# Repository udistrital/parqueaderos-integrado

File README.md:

#Parqueaderos
Es el entorno de desarrollo para el sistema de parqueaderos. Esta se inicia a través de un entorno de Vagrant.

Para iniciar la máquina:
```bash
$ vagrant up
```

Se ejecuta el aprovisionamiento de software base a la máquina:
```bash
$ vagrant provision
$ vagrant reload
$ vagrant ssh
```

¿MÁS FÁCIL?
-----------
```bash
$ ./install
```

INICIAR
-------
```bash
$ ./run
```

OTRAS OPCIONES
--------------
```bash
$ ./run --help
```

MODELO
------

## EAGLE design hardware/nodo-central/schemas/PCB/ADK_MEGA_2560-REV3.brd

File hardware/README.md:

# Módulo WIFI ESP8266
--------------------
Este módulo se comunica por protocolo serial (UART http://www.mbedded.ninja/electronics/communication-protocols/uart-protocol) a una taza predeterminada de 115200 baudios (bits por segundo https://www.arduino.cc/en/Serial/Begin).

* Guía rápida de inicio con el módulo WiFi ESP8266, contiene recomendaciones, conexiones y ejemplo de comandos AT se usa con Arduino UNO pero no se recomienda alimentación desde esta, se da alternativamente instrucciones para FTDI 3.3V Board. http://rancidbacon.com/files/kiwicon8/ESP8266_WiFi_Module_Quick_Start_Guide_v_1.0.4.pdf
* Se da una presentación de conexión de pines completa para todo el módulo, se realiza también una forma de actualizar el firmware del dispositivo. http://www.instructables.com/id/The-First-Usage-of-ESP8266-With-Arduino-Uno/
* Se destaca por dar un ejemplo de comandos AT. http://rayshobby.net/first-impression-on-the-esp8266-serial-to-wifi-module/
* Es el datasheet del integrado base, se destaca la muestra de potencia consumida en modo Transmisor, Receptor y en estados de hibernación. http://www.electroschematics.com/wp-content/uploads/2015/02/esp8266-datasheet.pdf
* Muestra de otra forma la documentación habitual, tiene documentación de los comandos AT sin ejemplos. https://nurdspace.nl/ESP8266
* Conexión del módulo for dummies (torpes). http://www.teomaragakis.com/hardware/electronics/how-to-connect-an-esp8266-to-an-arduino-uno/
* Se muestra un mapa conceptual de los comandos AT con ejemplos y una lista extendida de ellos. Referencias de documentación, características técnicas y la forma de actualizar el firmware. https://www.itead.cc/wiki/ESP8266_Serial_WIFI_Module
* Contiene información necesaria para configurar el módulo como un Access Point. http://dominicm.com/esp8266-configure-access-point/
* La wiki definitiva para los comandos AT: https://github.com/espressif/ESP8266_AT/wiki

# Módulo Ultrasonido MB1010 LV-MaxSonar®-EZ1
-------------------------------------------
Este módulo se utiliza para detectar la presencia o ausencia de objetos, este se puede controlar por medio de 3 métodos, el análogo, el PWM y con comunicación serial. El más acosejable es PWM (http://playground.arduino.cc/Main/MaxSonar).

* Documentación oficial de implementación del sensor. http://www.maxbotix.com/articles/085.htm
* Características técnicas del dispositivo sumado a enlaces del datasheet, explicaciones, guía de selección del sensores de la misma familia. https://www.sparkfun.com/products/8502
* https://sheldondwill.wordpress.com/2014/02/04/using-an-ultrasonic-sensor-hc-sr04-with-a-3-3v-micro-controller-tiva-c-series/

# Módulo RF 433MHz Transmisor y Receptor
---------------------------------------
* Enlaces de un transmisor RF dirigido a muchos Receptores. https://www.youtube.com/watch?v=h3OevEdl674 https://github.com/Simsso/Arduino-Wireless-Module-Multiple-Receivers
* Ideas de cómo conectar 20 sensores wireless a un solo receptor. Un transmisor solo emite cuando es necesario y puede retransmitir algunas veces con base de tiempo aleatorio para asegurarse de la llegada del dato. Las colisiones son bajas si la concurrencia de eventos no es baja. Se puede también transmitir a diferentes bases de tiempo para reducir el número de colisiones. http://electronics.stackexchange.com/questions/74272/how-to-connect-20-wireless-sensors-in-one-receiver-with-arduino
* Uso de la biblioteca rc-switch que sirve enviar códigos RC, sirve para controlar dispositivos de radio remoto. En este se consigue la información de 3 sensores de temperatura remotos para hacer un promedio de temperatura, se utilizan arduinos nano v3 y un display I2C, se muestra el código. http://www.electronicsmayhem.com/?p=68 https://github.com/sui77/rc-switch
* RF Link Receiver - 4800bps (434MHz), 500ft (152.4m) rango (en las mejores condiciones), 4800bps data rate, 5V supply voltage. https://www.sparkfun.com/products/10532
* RF Link Transmitter - 434MHz, 500ft (152.4m) rango (en las mejores condiciones), 4800bps data rate, 5V supply voltage. https://www.sparkfun.com/products/10534
* Tutorial completo de módulos RF para Arduino, código, conexiones y vídeos. http://www.instructables.com/id/RF-315433-MHz-Transmitter-receiver-Module-and-Ardu/?ALLSTEPS
* Breve documentación de la biblioteca VirtualWire. http://www.pjrc.com/teensy/td_libs_VirtualWire.html
* Se destaca por tener una comparación de dispositivos de Radio Frecuencia "económicos". http://www.raviyp.com/embedded/152-low-cost-zigbee-modules-for-using-in-projects
* 11 protocolos de internet de las cosas (IoT) sobre los que usted necesita saber. https://www.rs-online.com/designspark/eleven-internet-of-things-iot-protocols-you-need-to-know-about
* Hardware abierto para internet de las cosas. http://www.postscapes.com/internet-of-things-hardware/

# NRF24L01 transceptor 2.4-2.5GHz en la banda ISM (Industrial, Científico, Médico)
Este módulo transmite y recibe datos. Tiene un bajo consumo de potencia y el rango de trabajo del tensión es de 1.9 hasta 3.6 voltios. Tiene multiples frecuencas (125 puntos).
* https://hallard.me/nrf24l01-real-life-range-test/
* https://github.com/maniacbug/RF24
* https://harizanov.com/2013/06/nrf24l01-range-testing/
* http://playground.arduino.cc/InterfacingWithHardware/Nrf24L01
* https://arduino-info.wikispaces.com/Nrf24L01-Info
* http://www.nordicsemi.com/eng/Products/2.4GHz-RF/nRF24L01
* https://arduino-info.wikispaces.com/Nrf24L01-2.4GHz-HowTo?responseToken=fcd06dad835d084c7d89d1d4a147b989
* http://howtomechatronics.com/tutorials/arduino/arduino-wireless-communication-nrf24l01-tutorial/
* http://projectsfromtech.blogspot.com.co/2013/05/nrf24l01-arduino-communication-on.html
* http://howtomechatronics.com/tutorials/arduino/arduino-wireless-communication-nrf24l01-tutorial/
* http://projectsfromtech.blogspot.com.co/2013/05/nrf24l01-arduino-communication-on.html
* http://forum.arduino.cc/index.php?topic=131078.msg1331019#msg1331019

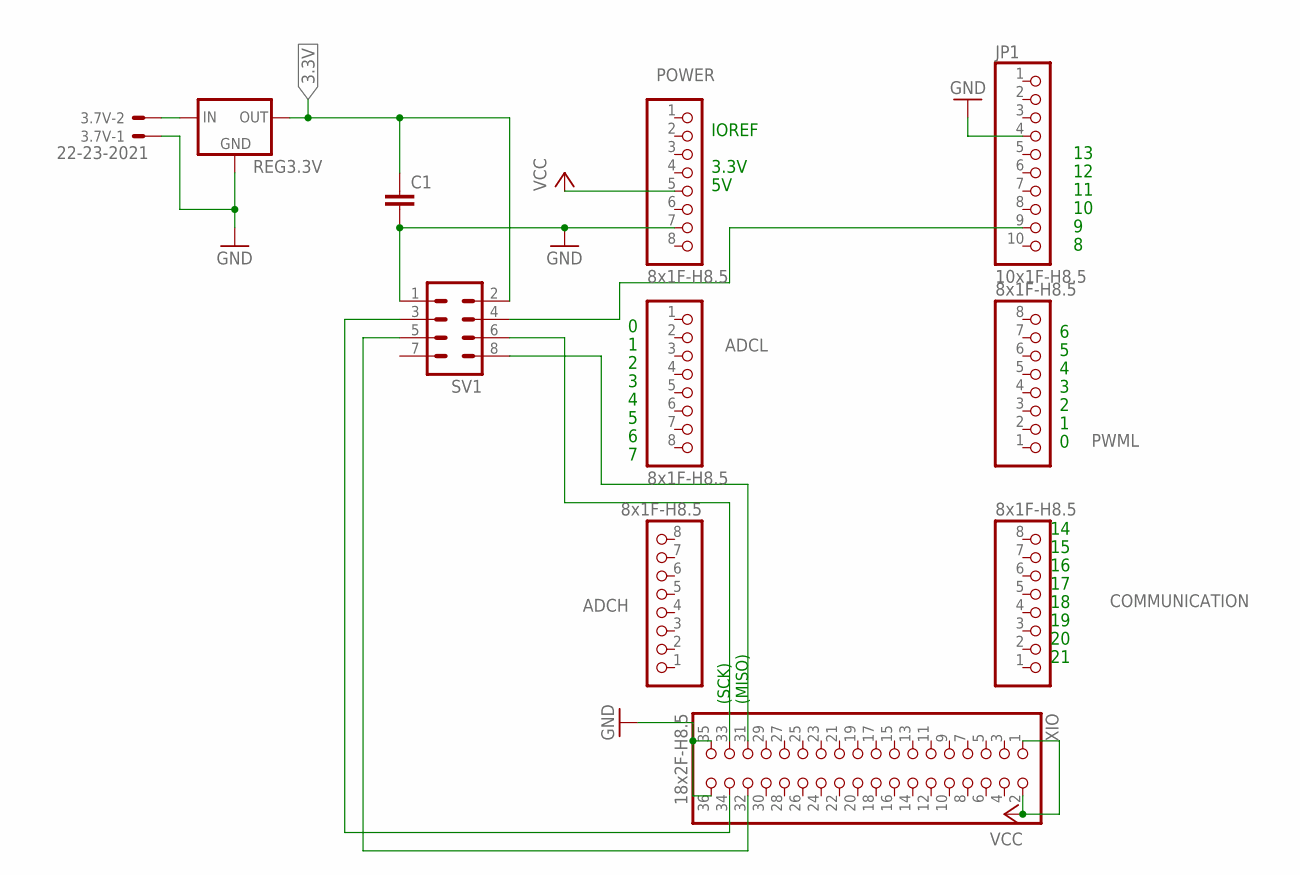
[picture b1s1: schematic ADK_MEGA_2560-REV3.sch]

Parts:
3.7V: 22-23-2021
ADCH: 8x1F-H8.5; 1X08
ADCL: 8x1F-H8.5; 1X08
C1: C-EU025-025X050; C025-025X050
COMMUNICATION: 8x1F-H8.5; 1X08
JP1: 10x1F-H8.5; 1X10
POWER: 8x1F-H8.5; 1X08
PWML: 8x1F-H8.5; 1X08
REG3.3V: 78XXL
SV1: MA04-2
XIO: 18x2F-H8.5; 2X18

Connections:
3.3V: C1.1, REG3.3V.OUT, SV1.2
GND: 3.7V.1, C1.2, JP1.4, POWER.7, REG3.3V.GND, SV1.1, XIO.35, XIO.36
unnamed: SV1.3, XIO.34
unnamed: SV1.5, XIO.32
unnamed: JP1.9, SV1.4
unnamed: SV1.6, XIO.33
unnamed: SV1.8, XIO.31
unnamed: 3.7V.2, REG3.3V.IN
VCC: POWER.5, XIO.1, XIO.2

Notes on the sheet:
(SCK)
(MISO)
IOREF
3.3V

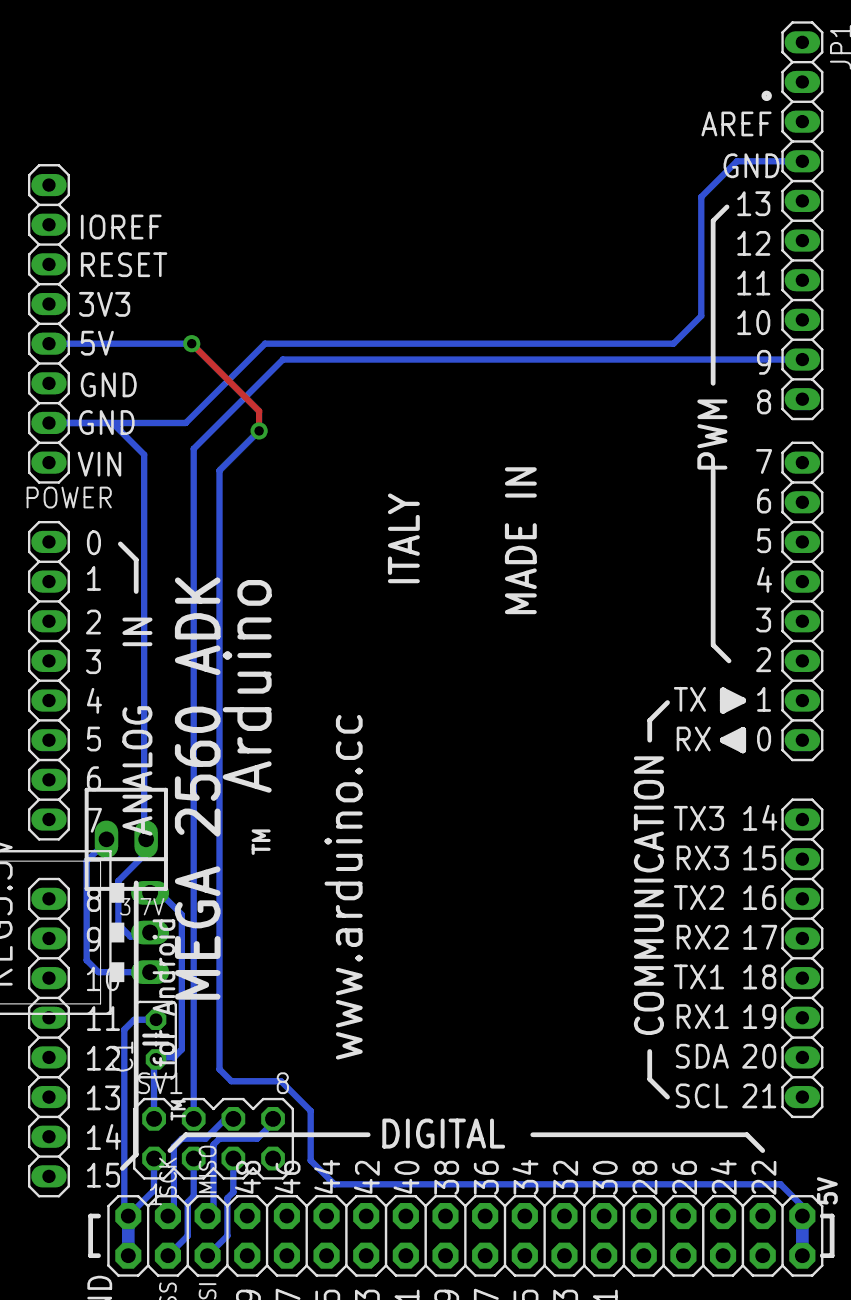
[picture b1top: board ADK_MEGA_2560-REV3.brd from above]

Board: 2 copper layers, 11 parts (0 on the bottom side), 9 nets.

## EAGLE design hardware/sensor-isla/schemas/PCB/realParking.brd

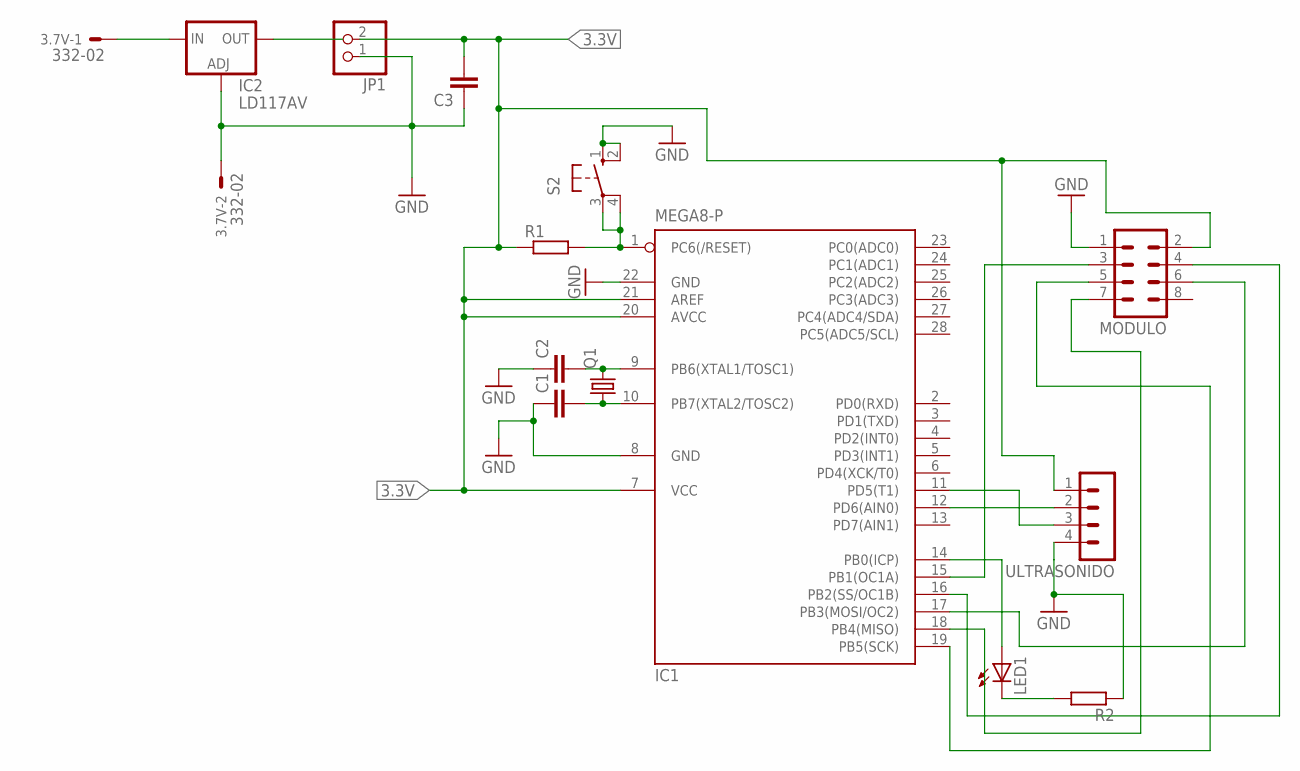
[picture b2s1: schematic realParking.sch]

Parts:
3.7V: 332-02
C1, C2, C3: C2,5-3; C2.5-3
IC1: MEGA8-P; DIL28-3
IC2: LD117AV; TO220L1
JP1: PINHD-1X2; 1X02
LED1: LED5MM
MODULO: MA04-2
Q1: CRYSTALTC26V; TC26V
R1, R2: R-EU_0204/5; 0204/5
S2: 10-XX; B3F-10XX
ULTRASONIDO: MA04-1

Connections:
3.3V: C3.2, IC1.7 (VCC), IC1.20 (AVCC), IC1.21 (AREF), JP1.2, MODULO.2, R1.1, ULTRASONIDO.1
GND: 3.7V.2, C1.1, C2.1, C3.1, IC1.8 (GND), IC1.22 (GND), IC2.1 (ADJ), JP1.1, MODULO.1, R2.1, S2.1 (S), S2.2 (S1), ULTRASONIDO.4
unnamed: 3.7V.1, IC2.3 (IN)
unnamed: IC1.12 (PD6(AIN0)), ULTRASONIDO.2
unnamed: IC1.11 (PD5(T1)), ULTRASONIDO.3
unnamed: LED1.K (C), R2.2
unnamed: IC1.14 (PB0(ICP)), LED1.A
unnamed: IC1.15 (PB1(OC1A)), MODULO.3
unnamed: IC1.16 (PB2(SS/OC1B)), MODULO.4
unnamed: IC1.17 (PB3(MOSI/OC2)), MODULO.6
unnamed: IC1.18 (PB4(MISO)), MODULO.7
unnamed: IC1.19 (PB5(SCK)), MODULO.5
unnamed: C2.2, IC1.9 (PB6(XTAL1/TOSC1)), Q1.2
unnamed: C1.2, IC1.10 (PB7(XTAL2/TOSC2)), Q1.1
unnamed: IC1.1 (PC6(/RESET)), R1.2, S2.3, S2.4 (P1)

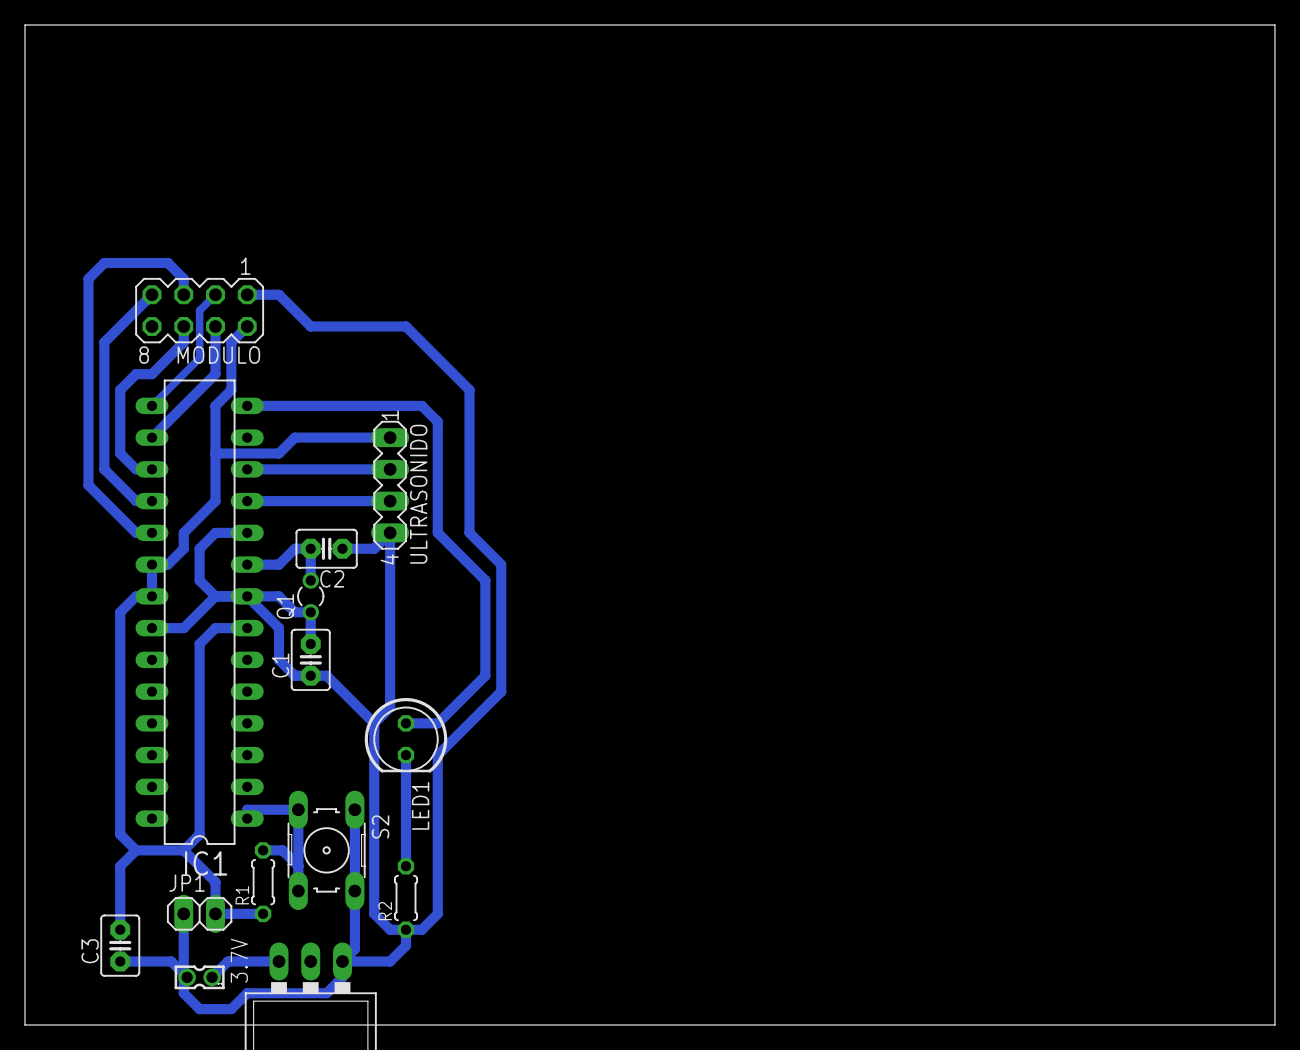
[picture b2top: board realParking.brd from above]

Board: 2 copper layers, 100.0 x 80.0 mm, 14 parts (0 on the bottom side), 15 nets.

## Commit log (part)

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2016-06-08 Se organizan los ficheros
2016-06-25 cambios para proxy
2016-06-25 Script funcionando
2016-07-12 ORM de Primera Propuesta de BD
2016-07-13 Se genera script de instalación de postgresql y script de parqueaderos
2016-07-13 Se mejoran los scripts y se corrigen sus errores
2016-07-13 Se generan otras utilidades
2016-07-14 Activacion de Migracion de DB
2016-07-18 mejoras a script instalación postgres, ip única
2016-07-18 Separando a virtualbox guest aditions en otro fichero
2016-07-18 fix postgresql instalation
2016-07-19 Se cambia la carpeta de desarrollo de data por src, ademas se realiza la segunda entrega de los ORM de la nueva base de datos propuesta, a traves de la modificacion del framework de beego.
2016-07-19 Ejecución de instrucción de construcción de tabla en una sola línea
2016-07-19 Se crea script de instalación del entorno
2016-07-19 Funciones para poner el proxy_ud
2016-07-19 Se actualiza para que cargue instalación de vboxaditions solo en caso de que el proveedor sea vbox
2016-07-19 Se quita beego
2016-07-19 compilación auto bee tool y mejora proxy_ud
2016-07-23 Se agregan las instruccion para comprobar el CRUD desde el backend
2016-07-23 Se relanza la version ReleaseTwo con las modificaciones ya comentadas para comprobar su funcionalidad quedando habilitada la misma
2016-07-26 actualizando readme
2016-07-30 Se reconfigura el Backend para funcionamiento con el Frontend (cors)
2016-07-30 Creacion del CRUD para el frontend con angularjs
2016-07-30 javascript con los controladores para el sitio web con ngResource para el consumo de RESTFull
2016-07-30 Template html basado en el layout general del sitio index.html, donde se muestran todos lor registros de la tabla de tipo_propietario
2016-07-30 Template html para la gestion de un registro en particular (ver, editar o eliminar) de la tabla tipo_propietario
2016-07-30 Captura de pantalla mostranto respuesta de Get One
2016-07-30 Captura de pantalla mostranto respuesta de Put
2016-08-03 Sistema de construcción de CRUD con yeoman
2016-08-05 Se mapean puertos y se instalan utilidades
2016-08-05 Se anexa prueba de uso de la herramiento generator-angular-go-martini
2016-08-05 directorios bin y pkg
2016-08-05 El paquete w3m no está en los repos, causaba fallo en la instalación
2016-08-05 script para instalar utilidades de npm
2016-08-05 Se crea script que crea automáticamente la base de datos
2016-08-05 El SQL debe estar disponible para ser modificado desde la máquina
2016-08-07 Se actualiza el readme
2016-08-07 Se agrega web-server en la ejecución del comando $ gulp
2016-08-08 Comandos ejecutados en la creación de CRUD tipo_propietario
2016-08-08 Fix permisos sobre db y selección db
2016-08-08 Comandos ejecutados para la creación de una API temporal para pruebas CRUD
2016-08-08 Registro de Yeoman generador CRUD
2016-08-08 Un script con instrucciones de uso del cliente
2016-08-08 Se actualiza el modelo de la base de datos en donde se definio para cada tabla como llave primario un dato indice
2016-08-08 Se agrega la v.1 del ORM para propietario (con las caracteristicas de los datos funcionando)
2016-08-08 Se agrega la v.1 del ORM para grupo_isla (con las caracteristicas de los datos funcionando)
2016-08-08 Se agrega la v.1 del ORM para grupo_isla (con las caracteristicas de los datos funcionando y los json completos)
2016-08-08 Se agrega la v.1 de la documentacion gestor de enrutamiento del backend
2016-08-08 Se elimina modelo de bases de datos anterior
2016-08-08 Se agrega v1 del controlador para la tabla propietario
2016-08-08 Se agrega v1 del controlador para la tabla grupo_isla
2016-08-08 Se agrega gestor de documentacion v1 del proyecto
2016-08-08 Se agrega codigo fuente y binario principal del proyecto v1 (el main del proyecto)
2016-08-08 Se agrega el fuente de bee/g_addcode.go modificado por particularidades del proyecto
2016-08-08 Se agregar gestores para la creacion de Frontend utilizando el generador de martini-go-angular
2016-08-08 Se agrega las librerias necesarios para el funcionamiento de FrontEnd (como las dependencia de AngularJs)
2016-08-08 Se agrega los estilos del FrontEnd
2016-08-08 Se agrega el template para propietario (CRUD) del FrontEnd
2016-08-08 Se agrega el template para grupo_isla (CRUD) del FrontEnd
2016-08-08 Se agrega el template para home del FrontEnd
2016-08-08 Se agrega el controlador para home del FrontEnd
2016-08-08 Se agrega el enrutador, controlador y la descripcion del servicio a consumir (REST-Full API) para propietario del FrontEnd
2016-08-08 Se agrega el enrutador, controlador y la descripcion del servicio a consumir (REST-Full API) para grupo-isla del FrontEnd
2016-08-11 Se agrega la restriccion de valores para IdTipoPropietario en la tabla Propietario (con select), como mecanismo de validacion de datos
2016-08-11 Se agrega la restriccion de valores para IdPropietario en la tabla Vehiculo (con select), como mecanismo de validacion de datos en la vista en el controller
2016-08-11 Se agrega la restriccion de valores para IdVehiculo y IdGrupoIsla en la tabla Isla (con select), como mecanismo de validacion de datos en la vista controller
2016-08-11 Para pruebas se deja sin CORS
2016-08-11 agregar gitignore en Cliente
2016-08-11 Eliminando binarios y logs
2016-08-11 Se ajusta para ejecutar tarea reload
2016-08-11 Se actualizan gitignore
2016-08-14 Se crea imagen y se asigna WKID al ente geográfico
2016-08-16 Se agrega al backend el mecanismo de validacion de datos para Tipo_Propietario
2016-08-17 Se corrige el mecanismo de validacion de datos para tipo_propietario
2016-08-17 Se anexa el mecanismo de validacion de datos para grupo_isla, se omite tipo Int
2016-08-17 Se anexa el mecanismo de validacion de datos para isla, se omite tipo Int y para llaves foraneas por misma restriccion
2016-08-17 Eliminando cliente antiguo
2016-08-17 geoserver as service to systemd
2016-08-17 Se mejoran los scripts de provisionamiento
2016-08-19 actualizando algunas preferencias de instalación de la app
2016-08-20 Configuración de desarrollo del subproyecto Visor Web Geográfico
2016-08-21 Update utilities script
2016-08-23 mapa funcionando
2016-08-23 Creando workspace parqueaderos
2016-08-23 add layer get and create not working
2016-08-28 actualiza nombre, traducciones y framework beego y bee
2016-08-28 hotfix configuración no cargada correctamente
2016-08-29 archivo de configuracion para conexion de base de datos
2016-08-29 traducción olvidada
2016-08-30 Corrigiendo formato con $ gofmt -w .
2016-08-30 router comments
2016-08-31 Se agrega archivo con parametros de funcionamiento de bower
2016-08-31 Se actualizan las dependencias de las librerias necesarias para el proyecto y se agrega bootstrap para responsividad
2016-08-31 Se modifica el controlador para correcto funcionamiento con angularjs 1.5.8: modal=>uimodal
2016-09-01 Se agrega la generacion de la hora para datos HoraEntrada y HoraSalida a traves de la time.now()
2016-09-01 Se modifica la vista del crub Isla para no solicitar los datos HoraEntrada y HoraSalida
2016-09-01 Se modifica el home del proyecto agregando el logo de la UD y mejorando su presentacion
2016-09-05 Visualización de capa vectorial, raster y osm
2016-09-06 Se halan capas isla y grupo_isla
2016-09-06 Se añaden los shapes al visor
2016-09-06 Se quita innecesario y se eliminan binarios no soportados por github, se excede geotiff y png georreferenciado
2016-09-07 imagen de la actualizacion de la base de datos
2016-09-07 Actualizacion de la base de datos
2016-09-07 Migracion de la base de datos creando la tabla registro a traves de migraciones en beego
2016-09-07 se agrega correccion de la ruta del controlador de la tabla registro
2016-09-07 Se agrega el modelo ORM de la tabla registro con beego
2016-09-07 Tooltips e iconos toc
2016-09-09 Se saca los comments de routers fuera del repo
2016-09-09 Se cambia puerto de geoserver en la instalación
2016-09-09 Se adiciona el script al provisionamiento de la máquina
2016-09-10 Se establece la funcionalidad del ORM de registro para el CRUD (Jsons completos y Datos tipo time generados automaticamente)
2016-09-14 Se actualiza el ORM de registro para la gestion de datos tipo time y construccion de json
2016-09-14 Se agrega el servicio para el CRUD de registro
2016-09-14 Se agrega el enrutador para el CRUD de registro
2016-09-14 Se agrega la vista del CRUD de la tabla registro en el frontend
2016-09-15 Se actualiza el controlador del CRUD de isla en el frontend
2016-09-16 Se corrige el direccionamiento de la pagina principal
2016-09-16 Se corrige el controlador de registro en el frontend
2016-09-16 Se corrige la vista de registro por mal identificacion del id=Id
2016-09-21 Se agrega en controlador del Login en el frontend
2016-09-21 Se agrega al index los scripts de Login
2016-09-21 Se agrega en controlador del login en el backend
2016-09-21 Se modifica el controlador de login adicionando la funcion JSONServer la cual tiene el mismo nombre de la funcion del framework para generar polimorfismo y asi no modificar el framework
2016-09-28 Se corrige error en la validacion del rango maximo del tamaño de una entrada con ngMaxlength
2016-09-28 Se corrige error en la sintaxis de ngMaxlength en la vista de Tipo_Propietarios
2016-09-28 Se corrige error en la sintaxis de ngMaxlength en la vista de Login
2016-09-28 Se agrega a las peticiones RETfull del frontend los encabezados para comprobacion y validacion de la cookie en el backend
2016-09-28 Se agrega error html 400 Bad Request a los json error
2016-10-03 Diagrama de Proceso Ingreso Automovil
2016-10-03 Fix diagrams
2016-10-04 Ejemplo de sensor ultrasonido
2016-10-04 Se agregan esquemas
2016-10-16 se agrega el codigo fuente para arduino, con la tarea de escribir y leer las etiquetas NFC
2016-10-16 Se agrega el codigo fuente de arduino para hacer peticion GET a traves de Ethernet
2016-10-18 Pruebas establecidas de conexión semifuncionales
2016-10-18 Se agrega un ejemplo funcional de la conexión
2016-10-18 Se agregan esquemas de conexión
2016-10-19 Se termina el Access Point por módulo wifi
2016-10-19 Diagrama pictórico N1
2016-10-20 Se agregan enlaces para leer y especificar funcionalidad
2016-10-23 Se agrega el mecanismo de encripcion de los datos
2016-10-23 Se crea el metodo para busqueda por isla en estado desocupado
2016-10-25 Se agregan cambios realizados sobre pruebas
2016-11-01 fixing bound
2016-11-02 Se actualiza on off capas
2016-11-02 Se agrega documentación, se corrige error.
2016-11-02 Se corrigen errores y se muestra más bonito
2016-11-02 Se agrega iframe visor
2016-11-02 Inicial code encryption/decryption (cifrar/descifrar) arduino
2016-11-06 Se documentan cambios en controller.go framework, se añade doc de hardware RF 2.4GHz, se agrega system service para iniciar backend de parqueaderos automáticamente
2016-11-08 Se agrega backend como servicio y se pone schema dentro de los parámetros de conexión
2016-11-08 Se corrige error, no redirigía a login
2016-11-15 Se documenta creación de gráficas.
2016-11-24 código del nodo central con recepción de 2 puntos
2016-11-24 código inicial del sensor para ATMEGA328
2016-11-25 Fix:Error en adquisición cookie
2016-11-26 código inicial y funcional del servicio web sse Server-Send Event
2016-11-26 Se modifica para consumir servicio sse, se codifica y se envia en HEX
2016-11-26 Agrego el código de otro tipo de cifrado AES CBC
2016-11-27 PProcesos de entrada y salida de motos, carros y bicicletas
2016-11-28 el nombre de las tablas siempre va en singular
2016-11-28 Se mueve de directorio porque inpide ejecución de bee run
2016-11-28 Se actualiza PCB con sensor y transceptor
2016-11-28 Arquitectura general del proyecto.
2016-11-28 Conectando bien el diagrama.
2016-12-01 se agrega presentación sin sozi
2016-12-01 Se le agrega un anuncio de gracias
2017-01-05 Fix errors
2017-01-10 Se agrega prueba de encriptado AES_CBC para el nodo central
2017-01-18 Se agrega codificacion hexadecimal al mensaje encriptado para prueba con arduino
2017-01-18 Se actualiza el servicio SSE y se le agrega descifrado AES_CBC
2017-02-06 Se realiza un proxy reverse para el servicio de geoserver.
2017-02-06 Se agrega función de Highlight (resaltar, colorear) La isla especificada.
2017-02-16 Se hace que el visor muestre el popup
